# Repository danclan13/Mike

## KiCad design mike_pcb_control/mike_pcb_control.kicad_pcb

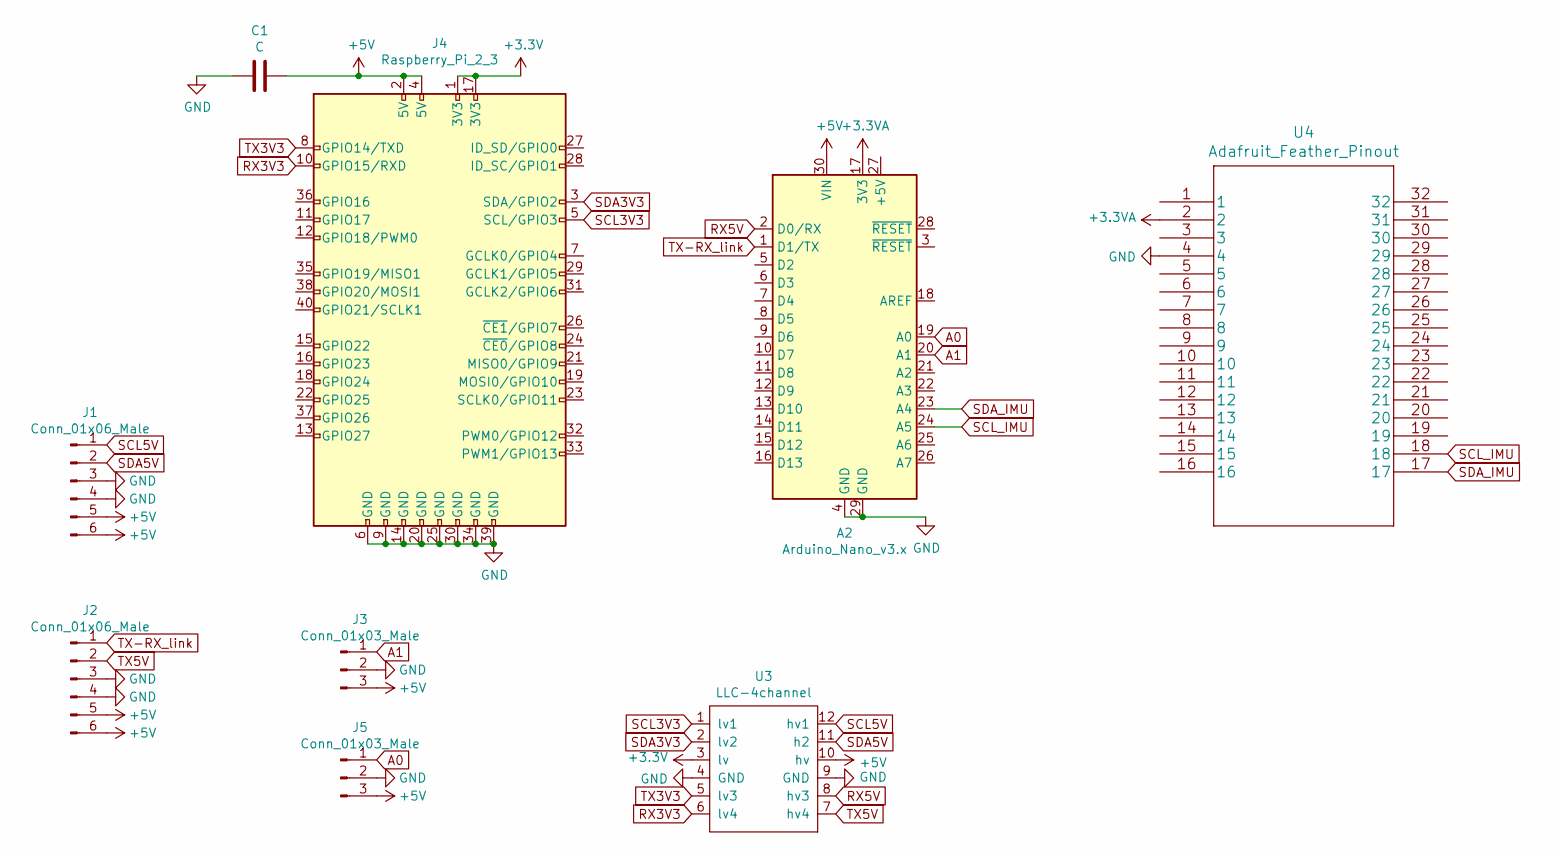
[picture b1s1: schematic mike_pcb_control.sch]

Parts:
A2: Arduino_Nano_v3.x; Arduino_Nano
C1: C; C_Radial_D8.0mm_H7.0mm_P3.50mm
J1, J2: Conn_01x06_Male; PinHeader_1x06_P2.54mm_Vertical
J3, J5: Conn_01x03_Male; PinHeader_1x03_P2.54mm_Vertical
J4: Raspberry_Pi_2_3; RasPi0,2,3-Header-upside_down
U3: LLC-4channel
U4: Adafruit_Feather_Pinout

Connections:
+3.3VA: A2.17 (3V3), U4.2
+3V3: J4.1 (3V3), J4.17 (3V3), U3.3 (lv)
+5V: A2.30 (VIN), C1.1, J1.5, J1.6, J2.5, J2.6, J3.3, J4.2 (5V), J4.4 (5V), J5.3, U3.10 (hv)
A0: A2.19 (A0), J5.1
A1: A2.20 (A1), J3.1
GND: A2.4 (GND), A2.29 (GND), C1.2, J1.3, J1.4, J2.3, J2.4, J3.2, J4.6 (GND), J4.9 (GND), J4.14 (GND), J4.20 (GND), J4.25 (GND), J4.30 (GND), J4.34 (GND), J4.39 (GND), J5.2, U3.4 (GND), U3.9 (GND), U4.4
RX3V3: J4.10 (GPIO15/RXD), U3.6 (lv4)
RX5V: A2.2 (D0/RX), U3.8 (hv3)
SCL3V3: J4.5 (SCL/GPIO3), U3.1 (lv1)
SCL5V: J1.1, U3.12 (hv1)
SCL_IMU: A2.24 (A5), U4.18
SDA3V3: J4.3 (SDA/GPIO2), U3.2 (lv2)
SDA5V: J1.2, U3.11 (h2)
SDA_IMU: A2.23 (A4), U4.17
TX3V3: J4.8 (GPIO14/TXD), U3.5 (lv3)
TX5V: J2.2, U3.7 (hv4)
TX-RX_link: A2.1 (D1/TX), J2.1

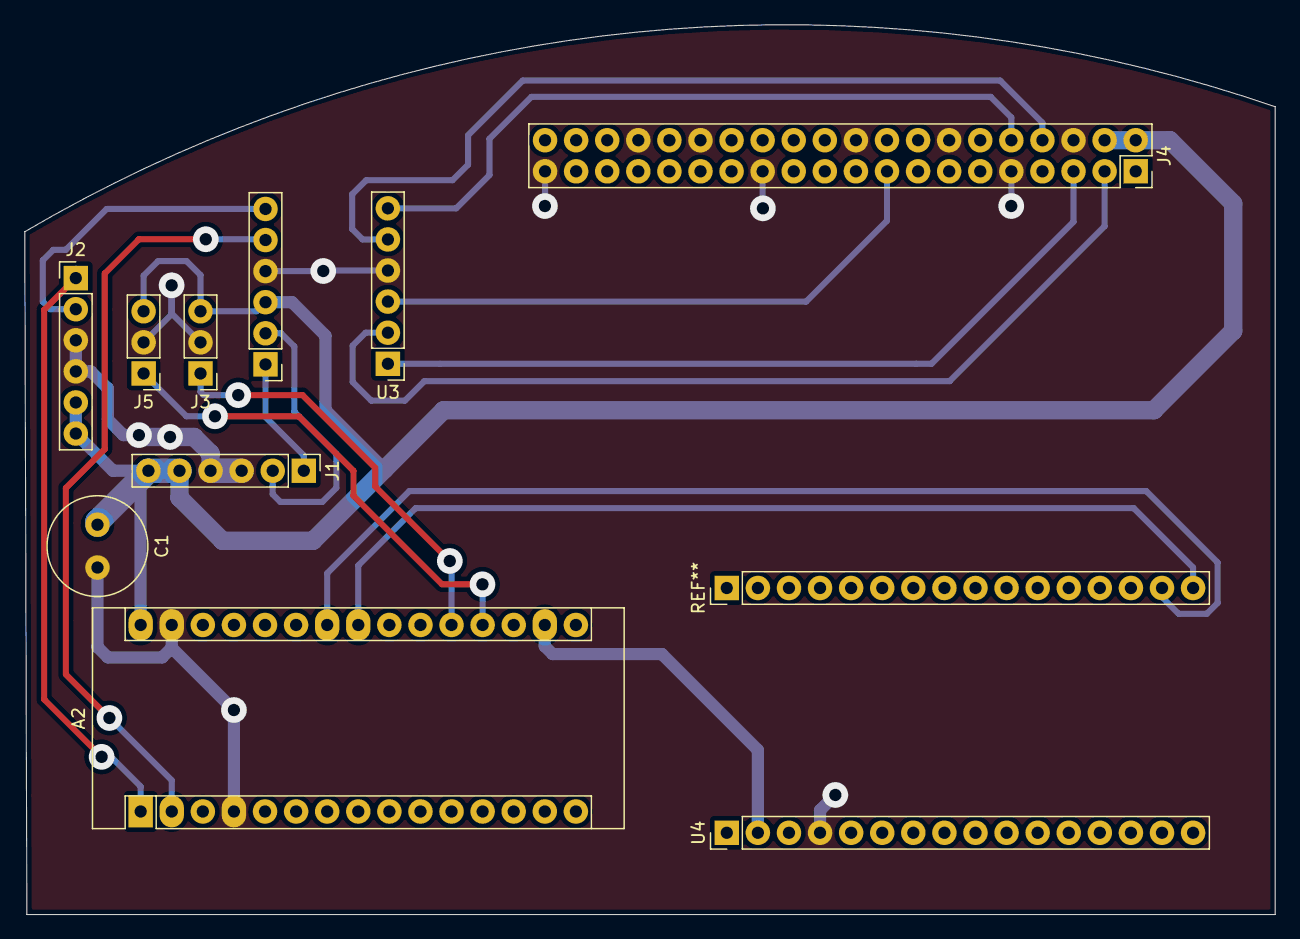
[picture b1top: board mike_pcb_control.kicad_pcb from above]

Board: 2 copper layers, 102.2 x 72.7 mm, 9 parts (0 on the bottom side), 17 nets.

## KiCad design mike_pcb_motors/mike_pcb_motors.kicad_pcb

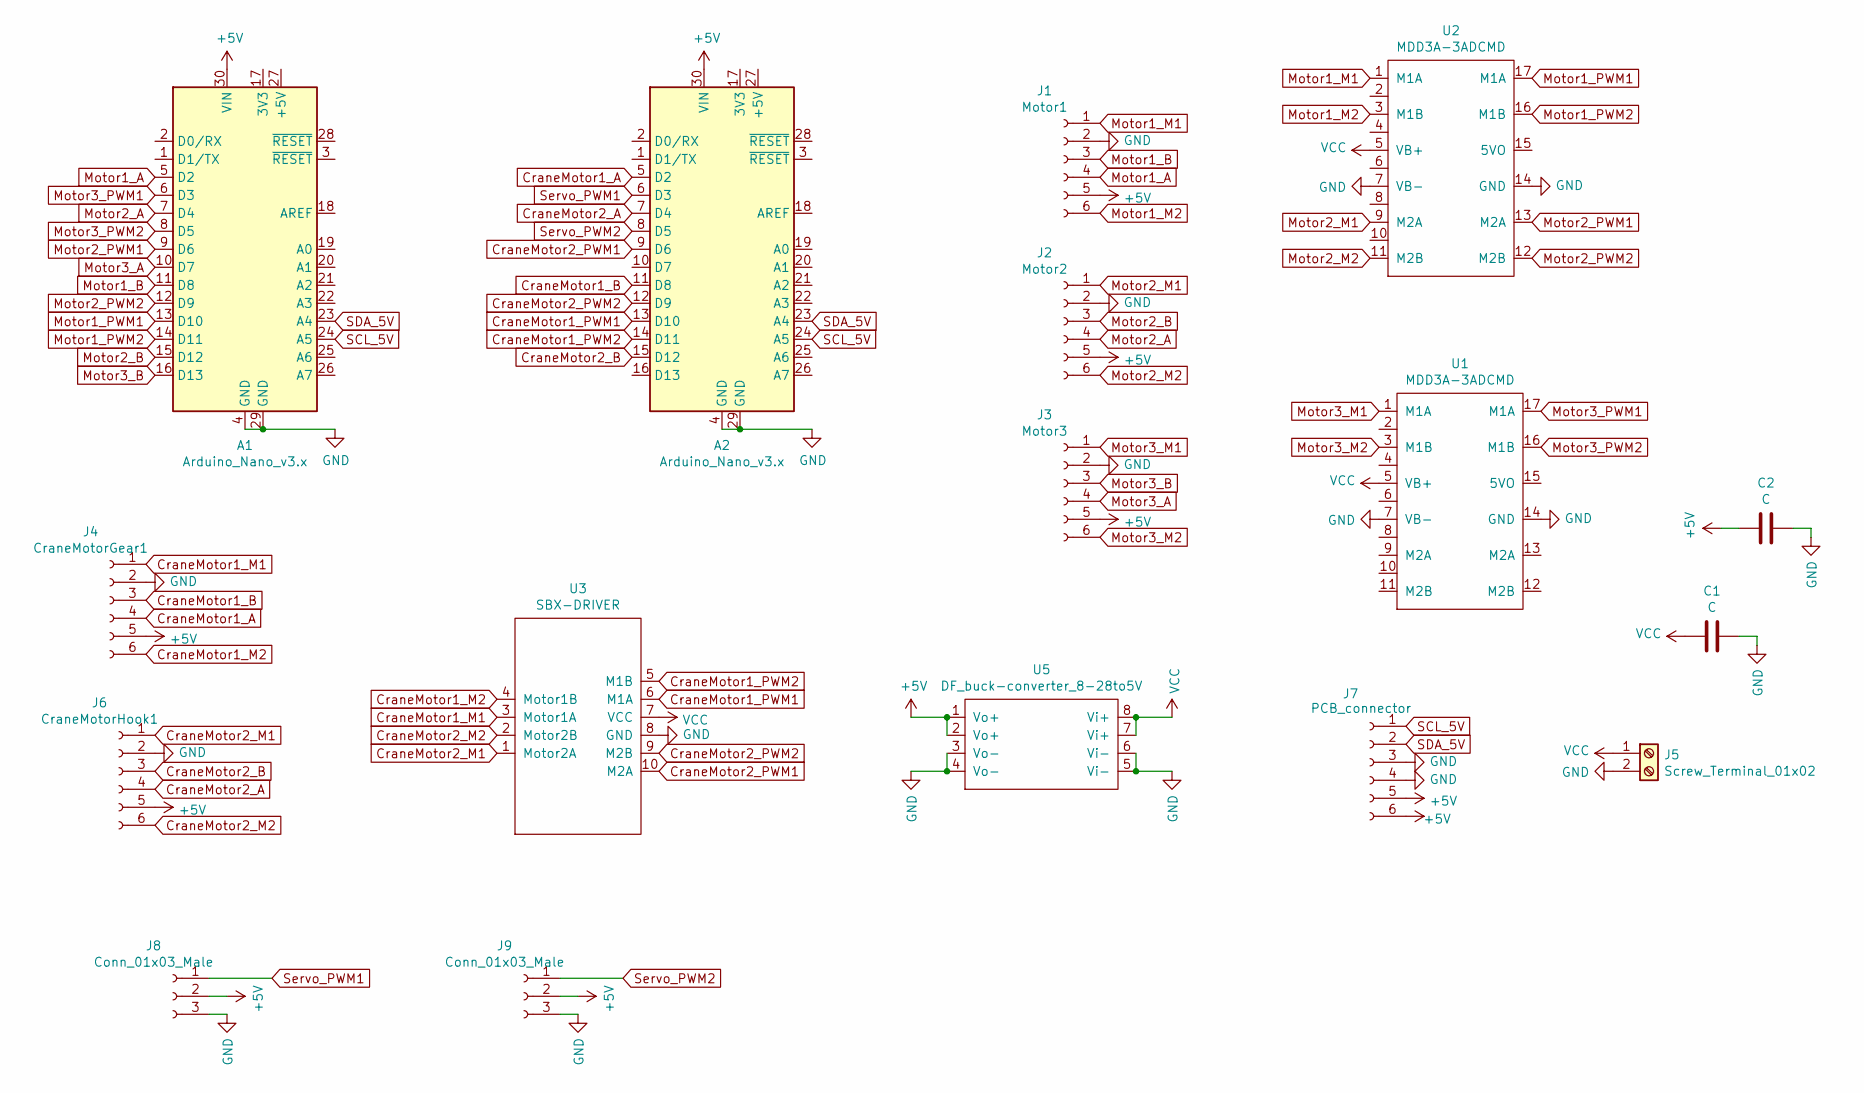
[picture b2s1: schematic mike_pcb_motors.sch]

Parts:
A1, A2: Arduino_Nano_v3.x; Arduino_Nano
C1, C2: C; C_Radial_D8.0mm_H7.0mm_P3.50mm
J1: Motor1; PinHeader_1x06_P2.54mm_Vertical
J2: Motor2; PinHeader_1x06_P2.54mm_Vertical
J3: Motor3; PinHeader_1x06_P2.54mm_Vertical
J4: CraneMotorGear1; PinHeader_1x06_P2.54mm_Vertical
J5: Screw_Terminal_01x02; TerminalBlock_bornier-2_P5.08mm
J6: CraneMotorHook1; PinHeader_1x06_P2.54mm_Vertical
J7: PCB_connector; PinHeader_1x06_P2.54mm_Vertical
J8, J9: Conn_01x03_Male; PinHeader_1x03_P2.54mm_Vertical
U1, U2: MDD3A-3ADCMD; mdd3a
U3: SBX-DRIVER
U5: DF_buck-converter_8-28to5V; DF_buck-converter_8-28to5

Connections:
+5V: A1.30 (VIN), A2.30 (VIN), C2.2, J1.5, J2.5, J3.5, J4.5, J6.5, J7.5, J7.6, J8.2, J9.2, U5.1 (Vo+), U5.2 (Vo+)
CraneMotor1_A: A2.5 (D2), J4.4
CraneMotor1_B: A2.11 (D8), J4.3
CraneMotor1_M1: J4.1, U3.3 (Motor1A)
CraneMotor1_M2: J4.6, U3.4 (Motor1B)
CraneMotor1_PWM1: A2.13 (D10), U3.6 (M1A)
CraneMotor1_PWM2: A2.14 (D11), U3.5 (M1B)
CraneMotor2_A: A2.7 (D4), J6.4
CraneMotor2_B: A2.15 (D12), J6.3
CraneMotor2_M1: J6.1, U3.1 (Motor2A)
CraneMotor2_M2: J6.6, U3.2 (Motor2B)
CraneMotor2_PWM1: A2.9 (D6), U3.10 (M2A)
CraneMotor2_PWM2: A2.12 (D9), U3.9 (M2B)
GND: A1.4 (GND), A1.29 (GND), A2.4 (GND), A2.29 (GND), C1.1, C2.1, J1.2, J2.2, J3.2, J4.2, J5.2, J6.2, J7.3, J7.4, J8.3, J9.3, U1.7 (VB-), U1.14 (GND), U2.7 (VB-), U2.14 (GND), U3.8 (GND), U5.3 (Vo-), U5.4 (Vo-), U5.5 (Vi-), U5.6 (Vi-)
Motor1_A: A1.5 (D2), J1.4
Motor1_B: A1.11 (D8), J1.3
Motor1_M1: J1.1, U2.1 (M1A)
Motor1_M2: J1.6, U2.3 (M1B)
Motor1_PWM1: A1.13 (D10), U2.17 (M1A)
Motor1_PWM2: A1.14 (D11), U2.16 (M1B)
Motor2_A: A1.7 (D4), J2.4
Motor2_B: A1.15 (D12), J2.3
Motor2_M1: J2.1, U2.9 (M2A)
Motor2_M2: J2.6, U2.11 (M2B)
Motor2_PWM1: A1.9 (D6), U2.13 (M2A)
Motor2_PWM2: A1.12 (D9), U2.12 (M2B)
Motor3_A: A1.10 (D7), J3.4
Motor3_B: A1.16 (D13), J3.3
Motor3_M1: J3.1, U1.1 (M1A)
Motor3_M2: J3.6, U1.3 (M1B)
Motor3_PWM1: A1.6 (D3), U1.17 (M1A)
Motor3_PWM2: A1.8 (D5), U1.16 (M1B)
SCL_5V: A1.24 (A5), A2.24 (A5), J7.1
SDA_5V: A1.23 (A4), A2.23 (A4), J7.2
Servo_PWM1: A2.6 (D3), J8.1
Servo_PWM2: A2.8 (D5), J9.1
VCC: C1.2, J5.1, U1.5 (VB+), U2.5 (VB+), U3.7 (VCC), U5.7 (Vi+), U5.8 (Vi+)

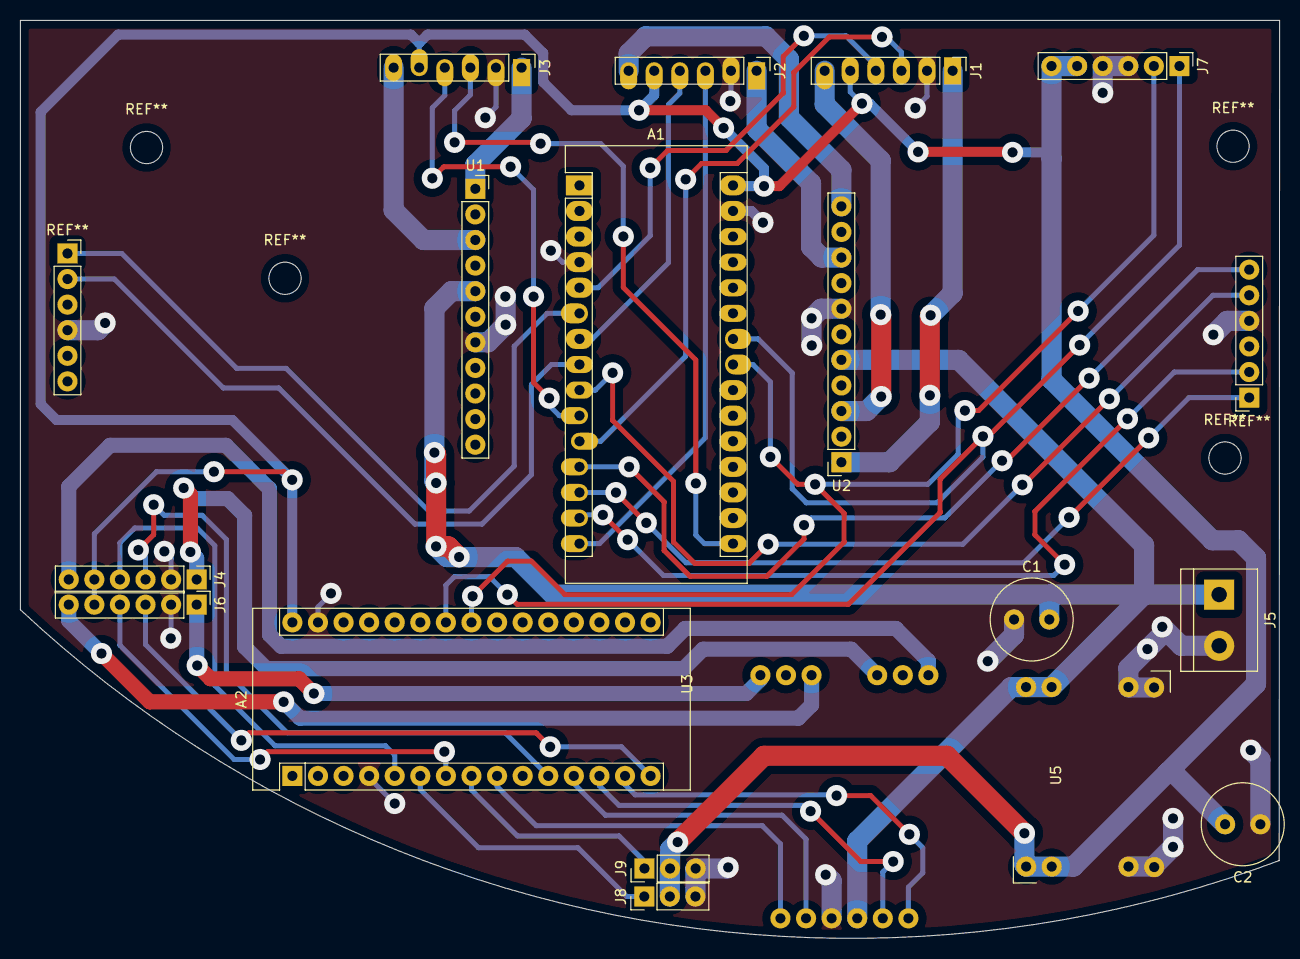
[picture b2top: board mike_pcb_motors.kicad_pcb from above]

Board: 2 copper layers, 125.0 x 91.1 mm, 17 parts (0 on the bottom side), 37 nets.

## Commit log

2021-12-16 Uploading the code
2021-12-16 Design files
2021-12-16 Updating the code
2021-12-17 Updating the files
2021-12-18 Added features
2021-12-18 Cad changes
2021-12-20 Updating the PCB files
2021-12-20 Updated cad
2021-12-21 Updating the physical design
2021-12-22 Cad update
2021-12-23 Cad update
    updated
2021-12-24 Updating the crane design files
2021-12-31 Updated design files
2022-01-04 Updating the design files
2022-01-05 Updating PCB files, baseplate file
2022-01-07 CAD update body, added distance senseor
2022-01-12 CAD changes
    Changes to top and bottom platform
2022-01-13 Updating the production files
2022-01-14 Small changes in the platform file
2022-01-19 Microswitch-model
2022-01-19 Updating the assembly
2022-01-21 Updating the code for the crane/arms arduino
2022-01-22 Cad change
2022-01-22 Pixy_arduino_sheild
2022-01-22 Updating the code and pcb files
2022-01-25 Uploading the updates
2022-01-25 PCB bugfix, I2C seperated
    I2C for IMU seperated from main I2C bus
2022-01-26 code updates
2022-01-28 Updating the crane code
2022-01-31 major update - line following working
2022-02-02 updated driving code
2022-02-03 unfinished course
